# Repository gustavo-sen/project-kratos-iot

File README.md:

# project-kratos-iot
A project to introduce IoT development in the new workspace

### Tecnologies
 - MQTT
 - Node-red
 - CXX

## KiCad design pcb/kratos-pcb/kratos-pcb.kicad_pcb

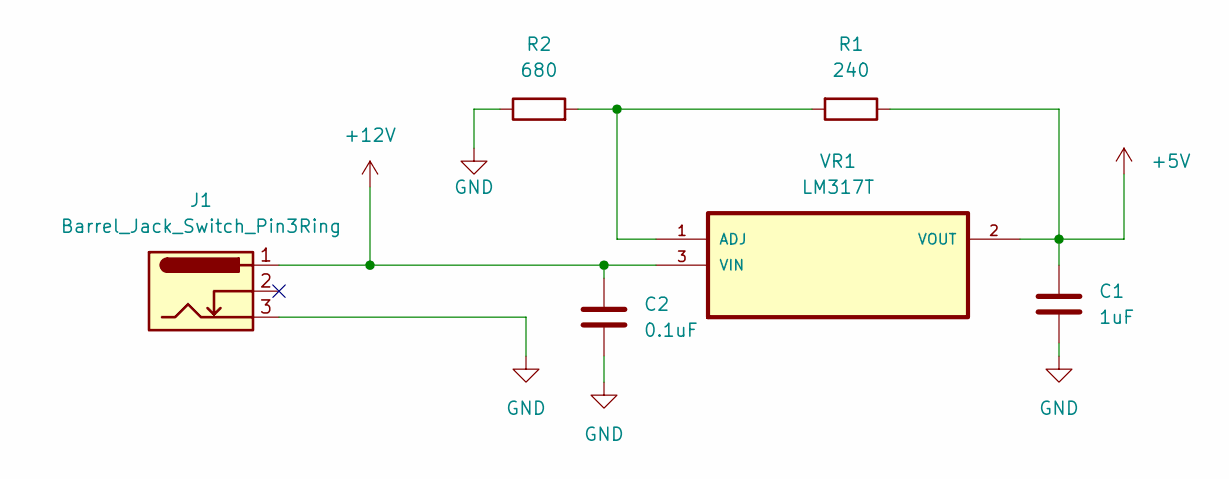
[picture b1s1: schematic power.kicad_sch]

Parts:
C1: 1uF; CP_Radial_D4.0mm_P1.50mm
C2: 0.1uF; C_Disc_D3.0mm_W1.6mm_P2.50mm
J1: Barrel_Jack_Switch_Pin3Ring; BarrelJack_Horizontal
R1: 240; R_Axial_DIN0204_L3.6mm_D1.6mm_P5.08mm_Horizontal
R2: 680; R_Axial_DIN0204_L3.6mm_D1.6mm_P5.08mm_Horizontal
VR1: LM317T; TO254P1054X470X1955-3

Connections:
+5V: C1.1, R1.1, VR1.2 (VOUT); also elsewhere on the board
+12V: C2.1, J1.1, VR1.3 (VIN); also elsewhere on the board
GND: C1.2, C2.2, J1.3, R2.1; also elsewhere on the board
unnamed: R1.2, R2.2, VR1.1 (ADJ)

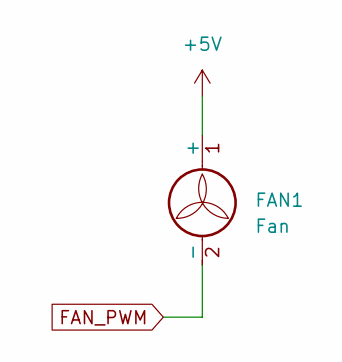
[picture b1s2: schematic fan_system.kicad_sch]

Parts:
FAN1: Fan; TerminalBlock_bornier-2_P5.08mm

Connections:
+5V: FAN1.1 (+); also elsewhere on the board
FAN_PWM: FAN1.2 (-); also elsewhere on the board

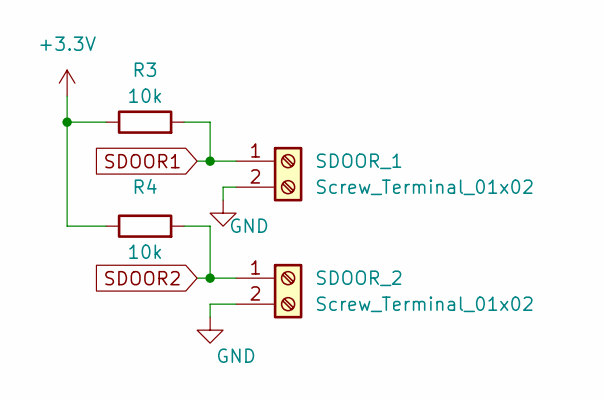
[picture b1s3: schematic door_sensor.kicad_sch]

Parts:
R3, R4: 10k; R_Axial_DIN0207_L6.3mm_D2.5mm_P10.16mm_Horizontal
SDOOR_1, SDOOR_2: Screw_Terminal_01x02; TerminalBlock_bornier-2_P5.08mm

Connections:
+3.3V: R3.1, R4.1; also elsewhere on the board
GND: SDOOR_1.2, SDOOR_2.2; also elsewhere on the board
SDOOR1: R3.2, SDOOR_1.1; also elsewhere on the board
SDOOR2: R4.2, SDOOR_2.1; also elsewhere on the board

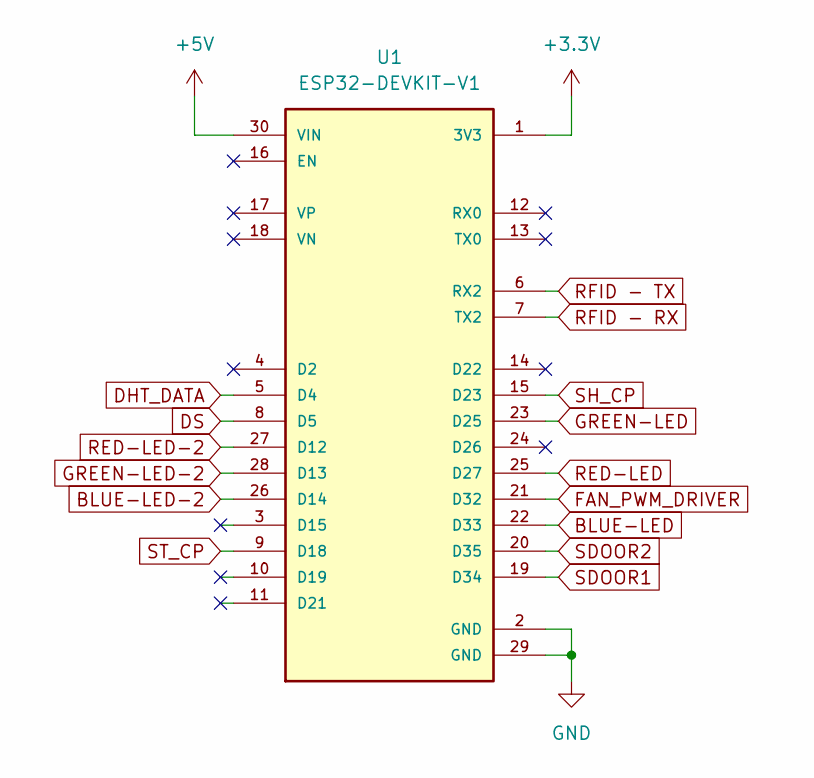
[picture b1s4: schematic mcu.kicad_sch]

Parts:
U1: ESP32-DEVKIT-V1; MODULE_ESP32_DEVKIT_V1; PARTREV N/A

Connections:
+3.3V: U1.1 (3V3); also elsewhere on the board
+5V: U1.30 (VIN); also elsewhere on the board
BLUE-LED: U1.22 (D33); also elsewhere on the board
BLUE-LED-2: U1.26 (D14); also elsewhere on the board
DHT_DATA: U1.5 (D4); also elsewhere on the board
DS: U1.8 (D5); also elsewhere on the board
FAN_PWM_DRIVER: U1.21 (D32); also elsewhere on the board
GND: U1.2 (GND), U1.29 (GND); also elsewhere on the board
GREEN-LED: U1.23 (D25); also elsewhere on the board
GREEN-LED-2: U1.28 (D13); also elsewhere on the board
RED-LED: U1.25 (D27); also elsewhere on the board
RED-LED-2: U1.27 (D12); also elsewhere on the board
SDOOR1: U1.19 (D34); also elsewhere on the board
SDOOR2: U1.20 (D35); also elsewhere on the board
SH_CP: U1.15 (D23); also elsewhere on the board
ST_CP: U1.9 (D18); also elsewhere on the board

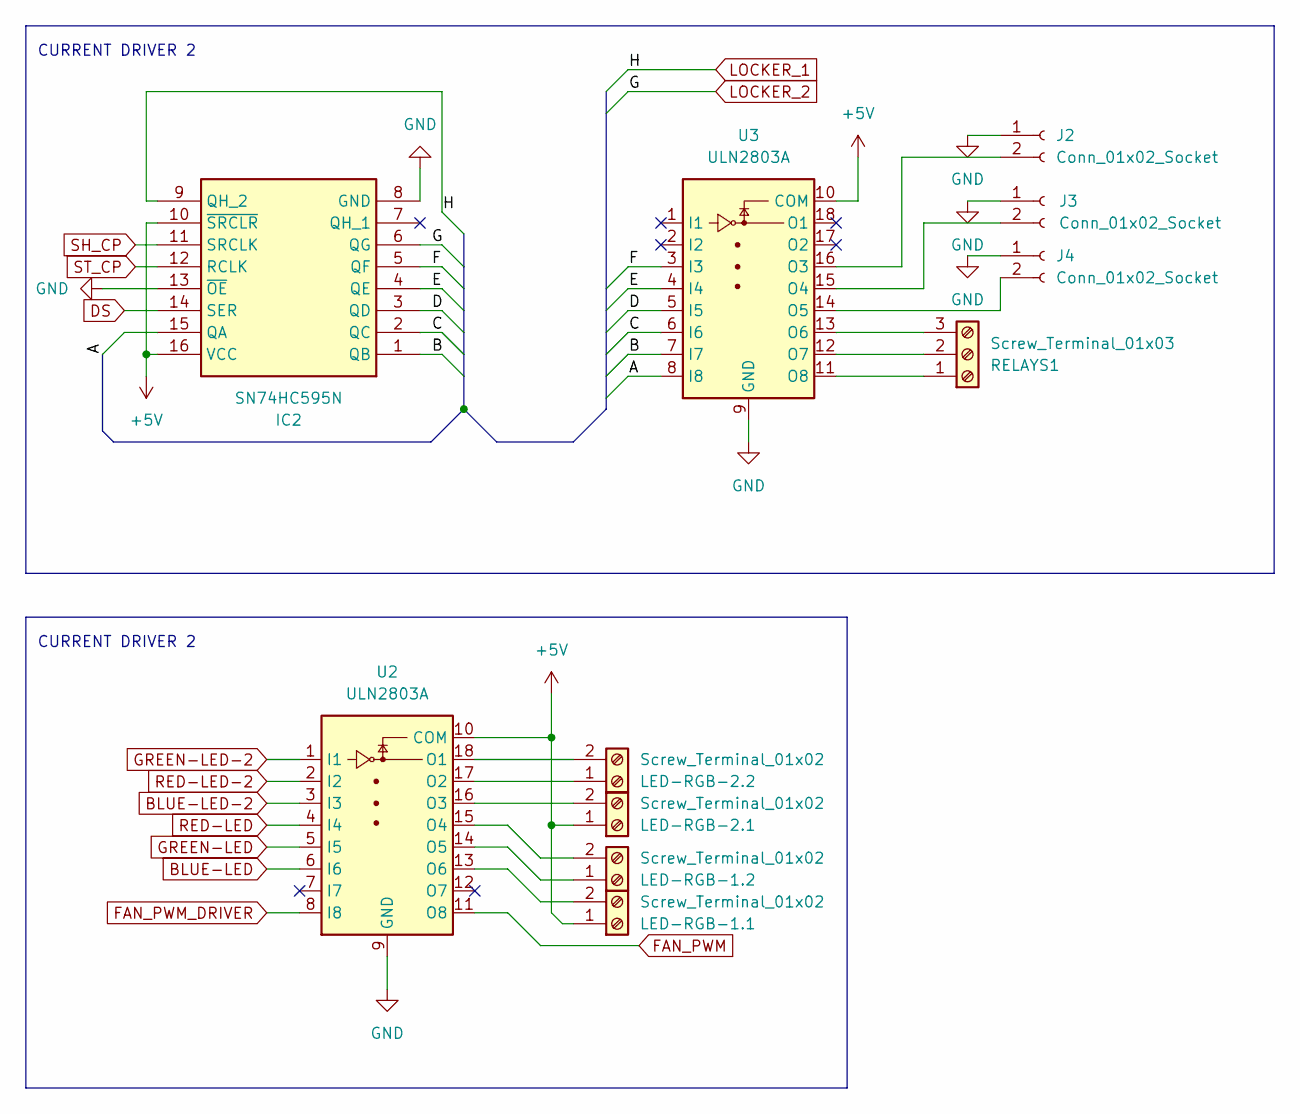
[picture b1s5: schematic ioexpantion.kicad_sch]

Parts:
IC2: SN74HC595N; DIP794W53P254L1930H508Q16N; Mouser Part Number 595-SN74HC595N
J2, J3, J4: Conn_01x02_Socket; PinSocket_1x02_P2.00mm_Vertical
LED-RGB-1.1, LED-RGB-1.2, LED-RGB-2.1, LED-RGB-2.2: Screw_Terminal_01x02; TerminalBlock_bornier-2_P5.08mm
RELAYS1: Screw_Terminal_01x03; TerminalBlock_4Ucon_1x03_P3.50mm_Horizontal
U2, U3: ULN2803A

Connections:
+5V: IC2.10 (~SRCLR), IC2.16 (VCC), LED-RGB-1.1.1, LED-RGB-2.1.1, U2.10 (COM), U3.10 (COM); also elsewhere on the board
/EXPANSION DRIVERS/A: U3.8 (I8)
/EXPANSION DRIVERS/B: IC2.1 (QB), U3.7 (I7)
/EXPANSION DRIVERS/C: IC2.2 (QC), U3.6 (I6)
/EXPANSION DRIVERS/D: IC2.3 (QD), U3.5 (I5)
/EXPANSION DRIVERS/E: IC2.4 (QE), U3.4 (I4)
/EXPANSION DRIVERS/F: IC2.5 (QF), U3.3 (I3)
BLUE-LED: U2.6 (I6); also elsewhere on the board
BLUE-LED-2: U2.3 (I3); also elsewhere on the board
DS: IC2.14 (SER); also elsewhere on the board
FAN_PWM: U2.11 (O8); also elsewhere on the board
FAN_PWM_DRIVER: U2.8 (I8); also elsewhere on the board
GND: IC2.8 (GND), IC2.13 (~OE), J2.1, J3.1, J4.1, U2.9 (GND), U3.9 (GND); also elsewhere on the board
GREEN-LED: U2.5 (I5); also elsewhere on the board
GREEN-LED-2: U2.1 (I1); also elsewhere on the board
LOCKER_1: IC2.9 (QH_2); also elsewhere on the board
LOCKER_2: IC2.6 (QG); also elsewhere on the board
unnamed: J2.2, U3.16 (O3)
unnamed: J3.2, U3.15 (O4)
unnamed: J4.2, U3.14 (O5)
unnamed: LED-RGB-1.1.2, U2.13 (O6)
unnamed: LED-RGB-1.2.1, U2.14 (O5)
unnamed: LED-RGB-1.2.2, U2.15 (O4)
unnamed: LED-RGB-2.1.2, U2.16 (O3)
unnamed: LED-RGB-2.2.1, U2.17 (O2)
unnamed: LED-RGB-2.2.2, U2.18 (O1)
unnamed: RELAYS1.1, U3.11 (O8)
unnamed: RELAYS1.2, U3.12 (O7)
unnamed: RELAYS1.3, U3.13 (O6)
RED-LED: U2.4 (I4); also elsewhere on the board
RED-LED-2: U2.2 (I2); also elsewhere on the board
SH_CP: IC2.11 (SRCLK); also elsewhere on the board
ST_CP: IC2.12 (RCLK); also elsewhere on the board

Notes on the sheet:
CURRENT DRIVER 2

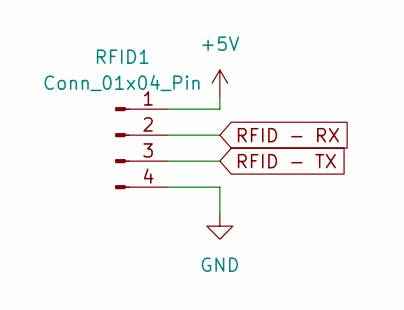
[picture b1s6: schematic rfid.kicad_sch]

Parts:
RFID1: Conn_01x04_Pin; PinHeader_1x04_P2.00mm_Vertical

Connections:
+5V: RFID1.1; also elsewhere on the board
GND: RFID1.4; also elsewhere on the board

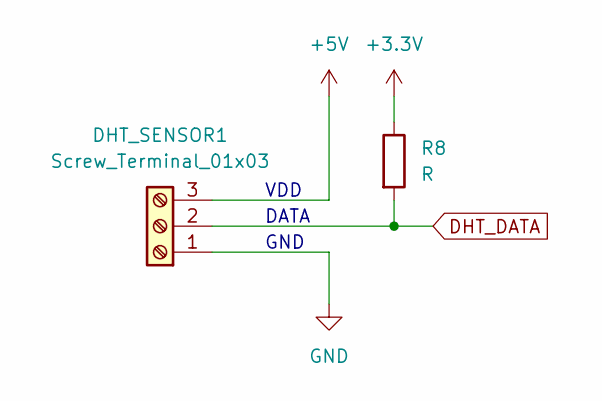
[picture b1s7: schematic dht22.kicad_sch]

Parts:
DHT_SENSOR1: Screw_Terminal_01x03; TerminalBlock_4Ucon_1x03_P3.50mm_Horizontal
R8: R; R_Axial_DIN0204_L3.6mm_D1.6mm_P5.08mm_Horizontal

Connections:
+3.3V: R8.1; also elsewhere on the board
+5V: DHT_SENSOR1.3; also elsewhere on the board
DHT_DATA: DHT_SENSOR1.2, R8.2; also elsewhere on the board
GND: DHT_SENSOR1.1; also elsewhere on the board

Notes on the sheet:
VDD
DATA
GND

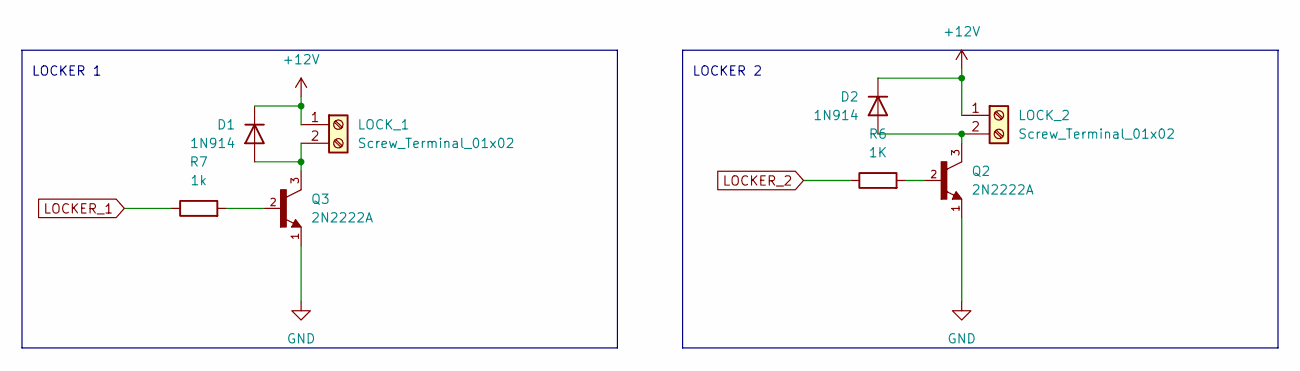
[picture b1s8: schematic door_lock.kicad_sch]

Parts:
D1, D2: 1N914; D_DO-35_SOD27_P7.62mm_Horizontal
LOCK_1, LOCK_2: Screw_Terminal_01x02; TerminalBlock_bornier-2_P5.08mm
Q2, Q3: 2N2222A; TO92254P470H750-3; PARTREV N/A
R6: 1K; R_Axial_DIN0204_L3.6mm_D1.6mm_P5.08mm_Horizontal
R7: 1k; R_Axial_DIN0204_L3.6mm_D1.6mm_P5.08mm_Horizontal

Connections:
+12V: D1.1 (K), D2.1 (K), LOCK_1.1, LOCK_2.1; also elsewhere on the board
GND: Q2.1, Q3.1; also elsewhere on the board
LOCKER_1: R7.1; also elsewhere on the board
LOCKER_2: R6.1; also elsewhere on the board
unnamed: D1.2 (A), LOCK_1.2, Q3.3
unnamed: D2.2 (A), LOCK_2.2, Q2.3
unnamed: Q2.2, R6.2
unnamed: Q3.2, R7.2

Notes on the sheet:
LOCKER 2
LOCKER 1

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
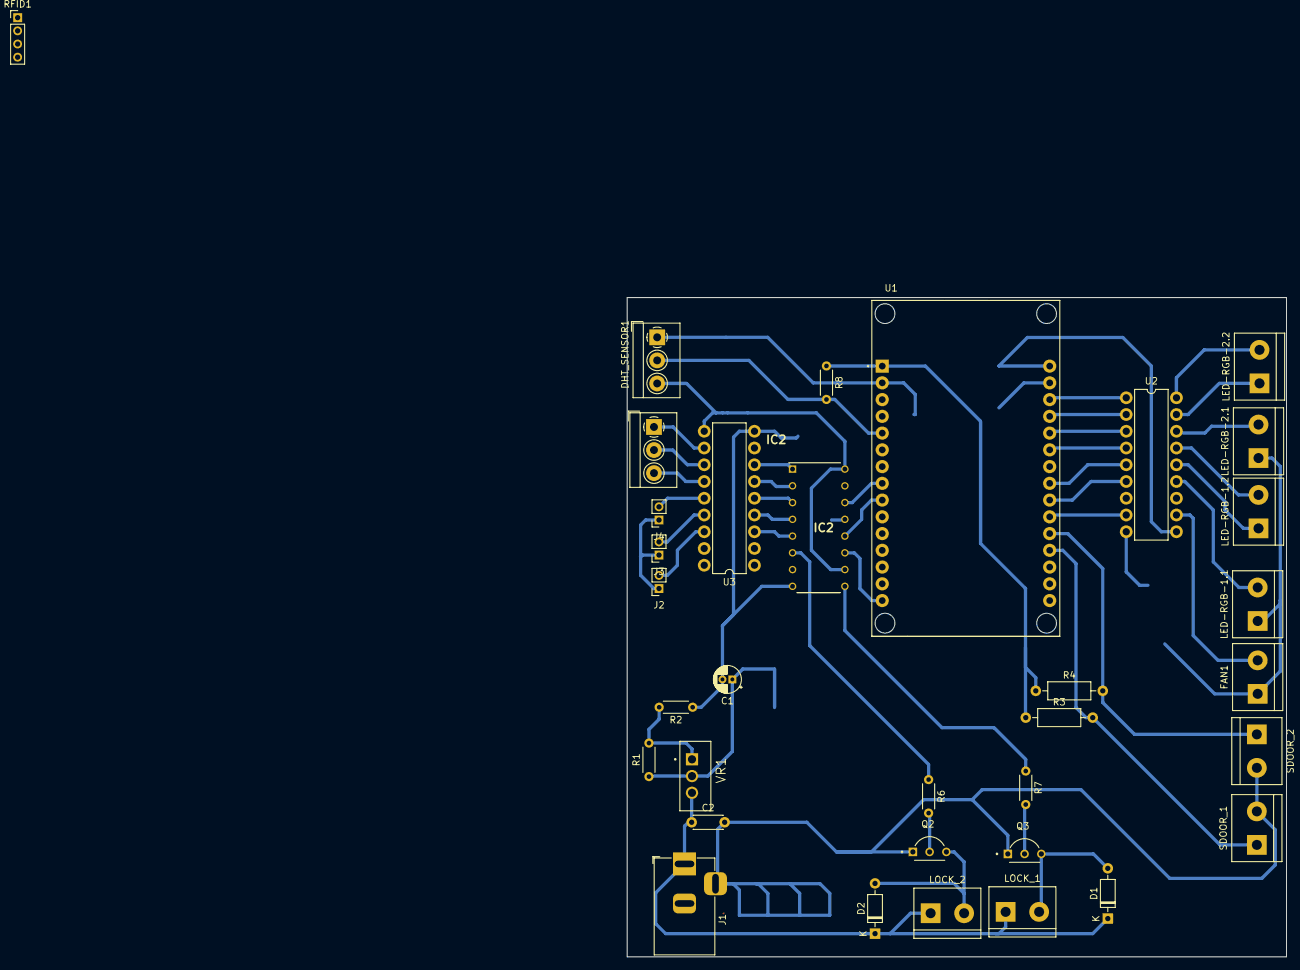
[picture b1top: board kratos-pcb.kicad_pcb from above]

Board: 2 copper layers, 100.0 x 100.0 mm, 34 parts (0 on the bottom side), 44 nets.

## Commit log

2024-02-03 Changes to be committed: new file: documentation/document.md new file: mcu/kratos-mcu/.gitignore new file: mcu/kratos-mcu/.vscode/extensions.json new file: mcu/kratos-mcu/include/README new file: mcu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
2024-02-03 test
2024-02-03 ## Added - source code for esp32 - docker red-node and mqtt mosquitto
2024-02-03 ## Removed - comments on docker file
2024-02-03 update gitigonre
2024-02-03 node-red gitignore
2024-02-03 ## Modified
    - README
2024-02-03 ### Remove - trash
2024-02-05 modified: mcu/kratos-mcu/src/main.cpp
2024-02-05 mqtt connection
2024-02-05 connection
2024-02-05 ### Added - mqtt_publish on mqtt_client
2024-02-06 adding multithread
2024-02-06 mqtt subscription function
2024-02-06 lamp controller
2024-02-07 ## Refactor - wifi function
2024-02-07 - lamp update
2024-02-07 #Removed - cleaning code
2024-02-07 lamp control
2024-02-07 remove iostream
2024-02-08 added kicad
2024-02-08 update git ignore
2024-02-08 gitignore logs
2024-02-09 added
2024-02-09 fix door_sensor_controller.cpp
2024-02-09 fix incorrect enum
2024-02-10 ## Fix - door_locker_controll.cpp logic
2024-02-10 fan controll
2024-02-10 ### Added - better ui
2024-02-11 ### Added fan comm
2024-02-11 ### UI
2024-02-12 #added
2024-02-13 ### added
    - pcb schematic
    - controller
2024-02-14 ### added - kicad components
2024-02-15 ### added nodered
2024-02-15 ### added - callback system
2024-02-15 ### added
2024-02-15 ### added - updated gitignore
2024-02-15 ### added - node-red-data/flows.json
2024-02-15 updated nodered and gitignore
2024-02-15 update kicad gitignore
2024-02-17 ### update - kicad schematic
2024-02-17 ### added - kicad simbols
2024-02-18 kicad
2024-02-18 corrections
2024-02-18 correct
2024-02-19 rgb implementation
2024-02-19 nodered
2024-02-19 ### MODIFY
2024-02-19 ## updatee
    - gitignor
2024-02-19 ### added - bitshift logic
2024-02-20 ### door sistem
2024-02-21 ### better layout
2024-02-21 removed
2024-02-22 ## test
2024-02-23 ### Modify - optmize code - corrections
2024-02-23 ### removed
2024-02-24 ### fix
2024-02-24 ### updated
2024-02-25 ### Modify - door sensor
    ### Removed
    - shift register remove comments
2024-02-25 ### Modify
    - schematic
